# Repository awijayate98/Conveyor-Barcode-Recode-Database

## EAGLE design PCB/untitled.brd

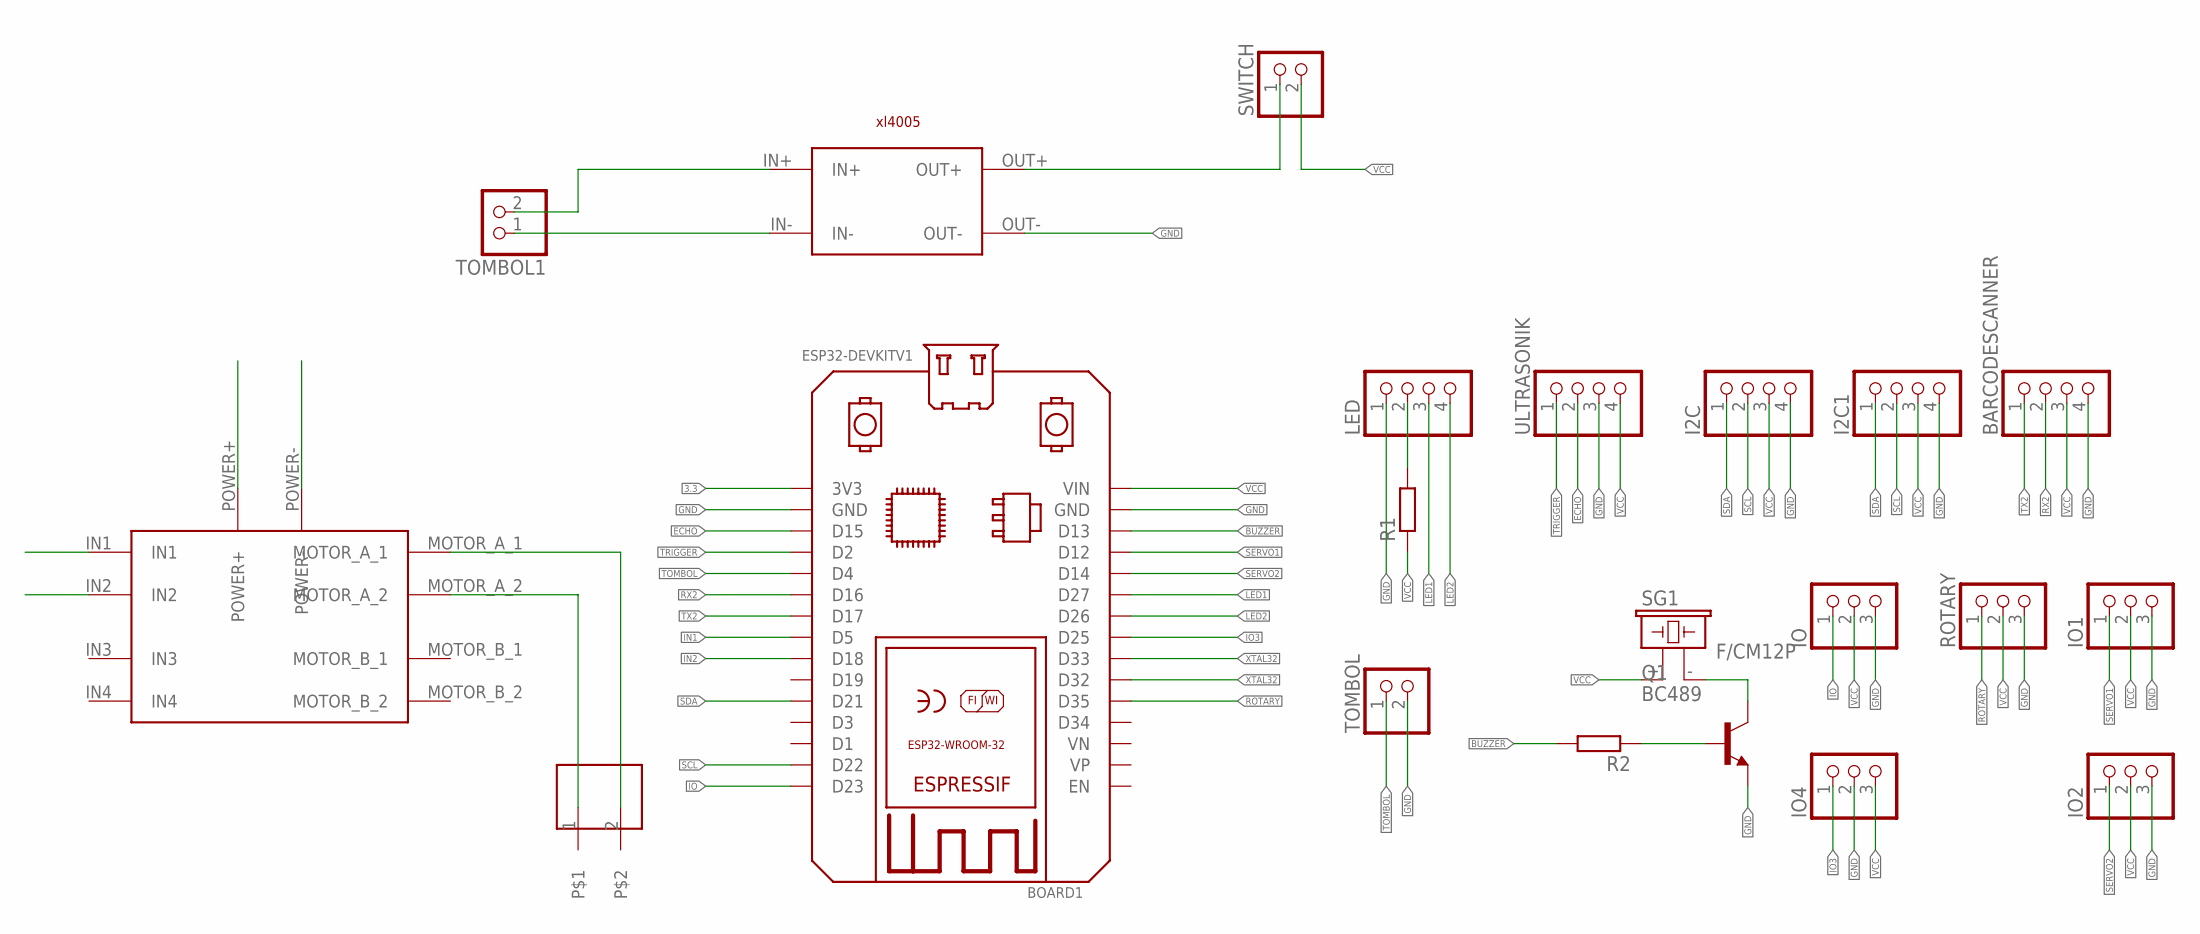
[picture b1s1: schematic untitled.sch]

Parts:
BARCODESCANNER: PINHD-1X4; 1X04
BOARD1: ESP32DEVKITV1SHRIDATTDUDHAT; ESP32-DEVKITV1
I2C, I2C1: PINHD-1X4; 1X04
IO, IO1, IO2, IO4: PINHD-1X3; 1X03
LED: PINHD-1X4; 1X04
Q1: BC489; TO92-EBC
R1, R2: R-EU_0207/10; 0207/10
ROTARY: PINHD-1X3; 1X03
SG1: F/CM12P
SWITCH: PINHD-1X2; 1X02
TOMBOL, TOMBOL1: PINHD-1X2; 1X02
U$1: DRIVERMOTOR_MINI
U$2: DC-STEP-DOWN-XL4005
U$3: TERMINALBLOCK2
ULTRASONIK: PINHD-1X4; 1X04

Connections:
3.3: BOARD1.3V3
BUZZER: BOARD1.D13, R2.2
ECHO: BOARD1.D15, ULTRASONIK.2
GND: BARCODESCANNER.4, BOARD1.GND, BOARD1.GND@1 (GND), I2C.4, I2C1.4, IO.3, IO1.3, IO2.3, IO4.2, LED.1, Q1.E, ROTARY.3, TOMBOL.2, U$1.POWER-, U$2.OUT-, ULTRASONIK.3
IN1: BOARD1.D5, U$1.IN1
IN2: BOARD1.D18, U$1.IN2
IO: BOARD1.D23, IO.1
IO3: BOARD1.D25, IO4.1
LED1: BOARD1.D27, LED.3
LED2: BOARD1.D26, LED.4
unnamed: TOMBOL1.1, U$2.IN-
unnamed: TOMBOL1.2, U$2.IN+
unnamed: LED.2, R1.2
unnamed: SWITCH.1, U$2.OUT+
unnamed: U$1.MOTOR_A_1, U$3.2
unnamed: U$1.MOTOR_A_2, U$3.1
unnamed: Q1.C, SG1.- (2)
unnamed: Q1.B, R2.1
ROTARY: BOARD1.D35, ROTARY.1
RX2: BARCODESCANNER.2, BOARD1.D16
SCL: BOARD1.D22, I2C.2, I2C1.2
SDA: BOARD1.D21, I2C.1, I2C1.1
SERVO1: BOARD1.D12, IO1.1
SERVO2: BOARD1.D14, IO2.1
TOMBOL: BOARD1.D4, TOMBOL.1
TRIGGER: BOARD1.D2, ULTRASONIK.1
TX2: BARCODESCANNER.1, BOARD1.D17
VCC: BARCODESCANNER.3, BOARD1.VIN, I2C.3, I2C1.3, IO.2, IO1.2, IO2.2, IO4.3, R1.1, ROTARY.2, SG1.+ (1), SWITCH.2, U$1.POWER+, ULTRASONIK.4
XTAL32: BOARD1.D32, BOARD1.D33

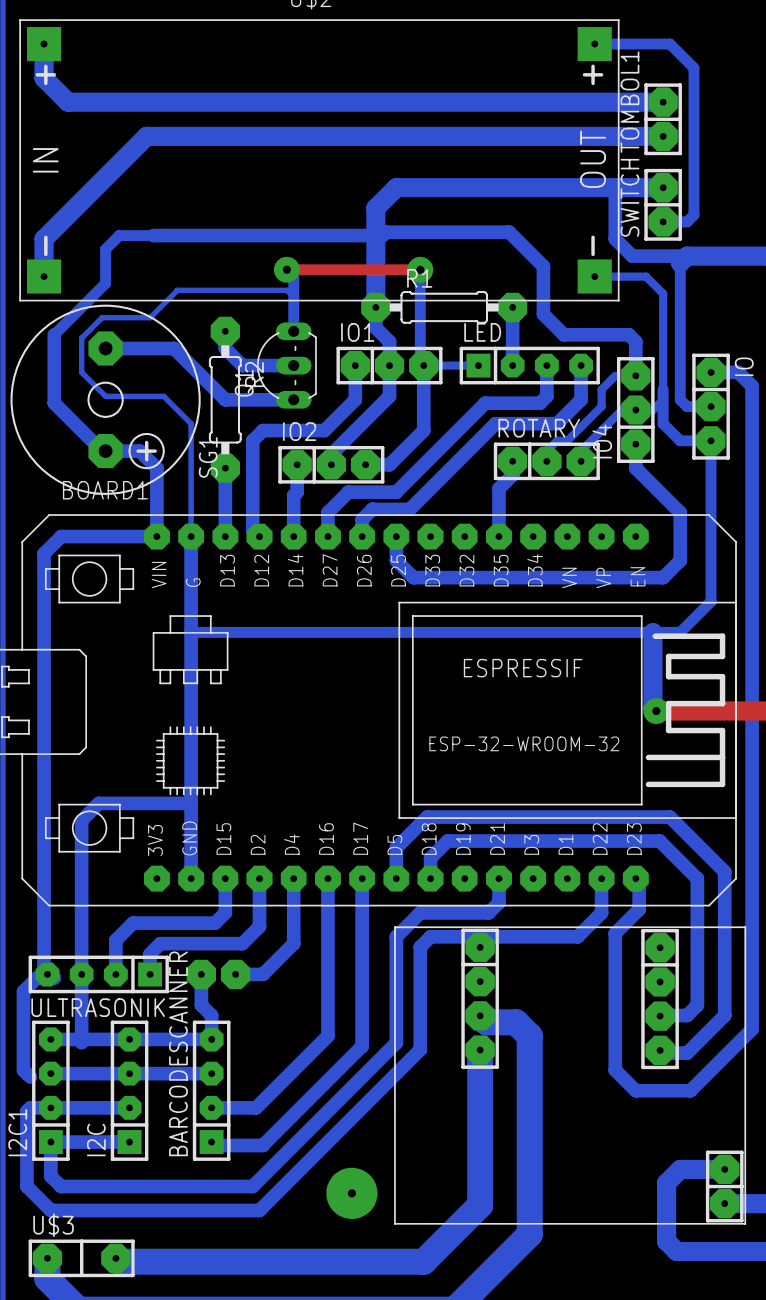
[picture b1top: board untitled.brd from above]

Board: 2 copper layers, 21 parts (1 on the bottom side), 28 nets.

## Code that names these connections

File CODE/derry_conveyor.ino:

#include <WiFi.h>
#include <AsyncTCP.h>
#include <ESPAsyncWebServer.h>
#include <ESPConnect.h>
#include <HTTPClient.h>
#include <ESP32Servo.h>
#include <Wire.h> 
#include <LiquidCrystal_I2C.h>
#include <Ultrasonic.h>
#include <ArduinoJson.h>

#define kiri 1
#define kanan 2
#define berhenti 0
#define plan_a 1
#define plan_b 2
#define servo_Pin1 23 //kiri
#define servo_Pin2 25 //kanan
#define motor1Pin1 18 
#define motor1Pin2 5 
#define echo 15
#define trigger 2
#define p_led1 12 //KUNING
#define p_led2 27 //HIJAU
#define p_potensio 35
#define tombol 4

static const int servoPin1 = servo_Pin1;
static const int servoPin2 = servo_Pin2;

char host_server[50] = "http://192.168.3.221/conveyorn";
String lok_kirim = "/config/post-esp.php?";
String lok_load = "/load.php";
int portserver = 80;
String api_key = "tPmAT5Ab3j7F1";

int distance,pot_value,val;
byte statusb;
String host_servers = "http://192.168.137.1/absen";
String kode="";
String label_kode="";
String k_barang1="8994214995547"; 
String k_barang2="8994214995543";
String label_barang1="ROKOK SAMPOERNA";
String label_barang2="SABUN LIFEBOY";
const int freq = 30000;
const int pwmChannel = 0;
const int resolution = 8;
int dutyCycle = 200;
int counter_barang;
int speedpwm = 200;
char datasend;
byte flag,cek,counter;
byte val_tombol,val_jarak;
int waitservo = speedpwm + 1100;
Servo servo1;
Servo servo2;
LiquidCrystal_I2C lcd(0x3F, 16, 2);
Ultrasonic ultrasonic(trigger,echo);
AsyncWebServer server(80);

void setup() 
{
    Serial.begin(115200);
    Serial2.begin(115200);
    Serial2.setTimeout(1000);
    lcd.begin();
    pinMode(motor1Pin1, OUTPUT);
    pinMode(motor1Pin2, OUTPUT);
    pinMode(p_led2, OUTPUT);
    pinMode(tombol, INPUT_PULLUP);
    ledcSetup(pwmChannel, freq, resolution);
    ledcAttachPin(motor1Pin1, pwmChannel);
    gerakmotor(0);
    ESPConnect.autoConnect("ESPConfig");
    if(ESPConnect.begin(&server)){
    Serial.println("Connected to WiFi");
    Serial.println("IPAddress: "+WiFi.localIP().toString());
    }else{
      Serial.println("Failed to connect to WiFi");
    }
    server.on("/", HTTP_GET, [&](AsyncWebServerRequest *request){
      request->send(200, "text/plain", "Hello from ESP");
    });
    request(1);
    server.begin();
    ESP32PWM::allocateTimer(2);
    ESP32PWM::allocateTimer(3);
    servo1.setPeriodHertz(50);    // standard 50 hz servo
    servo2.setPeriodHertz(50);    // standard 50 hz servo
    servo1.attach(servo_Pin1, 500, 2400); // attaches the servo on pin 18 to the servo object
    servo2.attach(servo_Pin2, 500, 2400); // attaches the servo on pin 18 to the servo object
    servo1.write(90);
    delay(1000);
    servo2.write(90);
    delay(1000);
    tampillcd(2);
}

void loop() 
{
  gerakmotor(kiri);
  bacasensor();
  Serial.println(val_jarak);
  bacagm66();
 if(val_jarak <=5)
  {
   kode ="";
   gerakmotor(0);
   delay(20);
   //bacagm66();
   }
}

void bacasensor()
{
  val_tombol = digitalRead(tombol);
  val_jarak = ultrasonic.read();
  if(val_tombol == 0)
  {
    delay(100);
    request(1);
  }
  
}
void bacagm66()
{
   if (Serial2.available() > 0) 
   {
    kode=Serial2.readStringUntil('\r');
    delay(50);
    if(kode.length()> 2)
    {
    Serial.print("terima data = ");
    Serial.println(kode);
    Serial.println(flag);
    Serial2.flush();
    cek = 0;
    flag = 1;
    olah_barang(); 
    delay(2000);
    gerakservo(0);
    tampillcd(2);
    kode = "";
    flag = 0;
    Serial2.flush();
    Serial.println(flag);
    cek = 0;
    counter_barang++;
    tampillcd(2);
    }
   }}


void gerakmotor(int b)
{
  if(b == kiri)
  {
    ledcWrite(pwmChannel, speedpwm);
    digitalWrite(motor1Pin1, HIGH);
    digitalWrite(motor1Pin2, LOW);
  }else if(b == kanan){
    ledcWrite(pwmChannel, speedpwm);
   digitalWrite(motor1Pin1, HIGH);
   digitalWrite(motor1Pin2, LOW);
  }else if(b == 0){
    ledcWrite(pwmChannel, 0);
    digitalWrite(motor1Pin1, LOW);
    digitalWrite(motor1Pin2, LOW);
  }else if(b == 4){
    ledcWrite(pwmChannel, 200);
    digitalWrite(motor1Pin1, LOW);
    digitalWrite(motor1Pin2, LOW);
  }
 
}


void olah_barang()
{
  label_kode = "";
    Serial.print("Label barang 1 = ");
  Serial.print(label_barang1);
  Serial.print(" ||  k_barang1 = ");
  Serial.println(k_barang1);
  Serial.print("Label barang 2 = ");
  Serial.print(label_barang2);
  Serial.print(" ||  k_barang1 = ");
  Serial.println(k_barang2);
  Serial.print("Speed = ");
  Serial.println(speedpwm);
  if((kode.equals(k_barang1)) || (kode.equals(k_barang2)))
  {
     if(kode.equals(k_barang1))
    {
      label_kode = label_barang1;
      tampillcd(1);
      delay(waitservo);
      gerakservo(plan_a);
    }else if(kode.equals(k_barang2))
    {
      label_kode = label_barang2;
      tampillcd(1);
      delay(waitservo);
      gerakservo(plan_b);
    }
  }else{
      label_kode = "Tidak terdaftar";
      tampillcd(1);
      gerakservo(0);
    }
    Serial.println(label_kode);
    request(0);
}

void gerakservo(int b)
{
    if(b == 0)
    {
      servo2.write(90);
      servo1.write(90);
    }else if(b == plan_a) //kriim ke kiri
    {
      servo1.write(130);
      servo2.write(180);
    }else if(b == plan_b){ //kririm ke kanan
      servo2.write(50);
      servo1.write(0);
  }
}

void tampillcd(int a)
{
  lcd.clear();
  if(a == 1)
  {
    lcd.setCursor(0,0);
    lcd.print("KODE=");
    lcd.print(kode);
    lcd.setCursor(0,1);
    lcd.print("BARANG=");
    lcd.print(label_kode);
  }else if( a == 2)
  {
    lcd.setCursor(0,0);
    lcd.print("KONVEYOR BARANG");
    lcd.setCursor(0,1);
    lcd.print("COUNTER=");
    lcd.print(counter_barang);
  }
}


void request(int a)
{
 if(WiFi.status()== WL_CONNECTED)
 {
    WiFiClient client;
    HTTPClient http;
//    
  if ( a == 0)
  {
    lcd.clear();
    lcd.setCursor(0,0);
    lcd.print("Update");
    String urlserver = String(host_server)+lok_kirim+"api_key="+api_key+"&kode="+kode;
    lcd.clear();
    http.begin(client,urlserver.c_str());
    Serial.println(urlserver.c_str());
    int httpResponseCode = http.GET();
    lcd.setCursor(0,1);
    lcd.print(httpResponseCode);
    if(httpResponseCode == 200 )
    {
      Serial.println("DATA TERKIRIM");
//      digitalWrite(led_hijau,LOW);
    }
    urlserver = "";
  }else 
if(a==1)
  {
    digitalWrite(p_led2, HIGH);
    String hostsetting = String(host_server)+lok_load;
    http.begin(client,hostsetting);
    int httpCode = http.GET();            //Send the request
    Serial.println(httpCode);
    if (httpCode == 200) 
    {
      String payload = http.getString();
      Serial.println(payload);
      StaticJsonDocument<256> doc;
      DeserializationError error = deserializeJson(doc, payload);
      if (error) {
        Serial.print("deserializeJson() failed: ");
        Serial.println(error.c_str());
        return;
      }
      JsonObject root_0 = doc["0"];
      label_barang1 = root_0["namabarang1"].as<String>(); // "sss"
      k_barang1 = root_0["kodebarang1"].as<String>(); // "22222222222222"
      label_barang2 = root_0["namabarang2"].as<String>(); // "dddd"
      k_barang2 = root_0["kodebarang2"].as<String>(); // "333444444"
      speedpwm = root_0["kecepatan"]; // "200"
      const char* root_0_id = root_0["id"]; // "1"
      counter_barang = doc["jumlah"]; // "6"
      Serial.print("Label barang 1 = ");
      Serial.print(label_barang1);
      Serial.print(" ||  k_barang1 = ");
      Serial.println(k_barang1);
      Serial.print("Label barang 2 = ");
      Serial.print(label_barang2);
      Serial.print(" ||  k_barang2 = ");
      Serial.println(k_barang2);
      Serial.print("Speed = ");
      Serial.println(speedpwm);
      digitalWrite(p_led2, LOW);
    }
   http.end();
  }
 }

}

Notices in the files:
parts and their libraries:
diy-modules: Released under the Creative Commons Attribution 4.0 International License: http://creativecommons.org/licenses/by/4.0
